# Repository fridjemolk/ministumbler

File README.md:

# ministumbler, a tiny ESP32 WiFi stumbling tool

This repo contains arduino code, helper python scripts, KiCad and Gerber Files, and hardware information about my ESP32 based WiFi stumbler, designed with low cost, minimal size, and easy of asssembly in mind. It is currently based around the Seeed XIAO/Adafruit QT Py ecosystem.

As of 02/2026, this project exists in 3 different hardware configurations, all of which are based on a GNSS Module, a MicroSD card slot, and a Xiao ESP32-S3:

#### v0.2: A custom PCB backplane supporting each of the modules, plus a [LiPo battery](https://thepihut.com/products/2000mah-3-7v-lipo-battery) charged by the Xiao ESP32-S3's built-in charge circuit, designed to fit into [this case from the Pi Hut](https://thepihut.com/products/small-plastic-project-enclosure-weatherproof-with-clear-top). The KiCad and Gerber files are [available here.](https://github.com/fridjemolk/ministumbler/tree/master/ministumbler_weatherproof_case) 

#### v0.1: A custom flex PCB backplane, supporting each of the modules, designed for stealthy use in the pocket of a bag or inside clothing. The KiCad and Gerber files are [available here.](https://github.com/fridjemolk/ministumbler/tree/master/ministumbler_kicad)

#### v0: A soldered-together stack of all three modules into a very compact rough cube shape. This was the initial prototype and is a little awkward to assemble as it requires deliberately not soldering certain pins for each module. 

All three hardware versions currently [use the same firmware](https://github.com/fridjemolk/ministumbler/blob/master/Ministumbler_WiGLE/Ministumbler_WiGLE.ino), with the same pin configurations, requireing the TX jumper pad to be **CUT** on the SD module and the A1 jumper pad **SOLDERED**. This firmware builds off the firmware created by [lozaning](https://github.com/lozaning) for their [Wifydra Project](https://github.com/lozaning/The_Wifydra), so credit to them for all their hard work in supporting the WiGLE CSV format and handling SD card file creation and management. 

[As of 02/2026, this is the main firmware used for this project](https://github.com/fridjemolk/ministumbler/blob/master/Ministumbler_WiGLE/Ministumbler_WiGLE.ino)

### Required Hardware

#### In the current design version the following three boards are used:

- [Seeed XIAO ESP32S3.](https://wiki.seeedstudio.com/xiao_esp32s3_getting_started/) The S3 variant of the ESP32 has the added benefit of Bluetooth support, and of having a U.FL connector for an external antenna, opening up options for optimising reception. Alternatively, the [Seeed XIAO ESP32C5](https://www.seeedstudio.com/Seeed-Studio-XIAO-ESP32C5-p-6609.html) can be used if 5GHz WiFi support is required, as both boards use the same pinout, however 5GHz is not yet supported by the firmware in this repo.
- [L76K GNSS Module for SeeedStudio XIAO.](https://wiki.seeedstudio.com/get_start_l76k_gnss/) A low-cost, TinyGPS++ compatible GPS module that has proven easy to use and quick to lock. Includes an active GPS antenna, also connected via a U.Fl connector
- [Adafruit microSD Card BFF.](https://learn.adafruit.com/adafruit-microsd-card-bff) A basic microSD card breakout board from adafruit that directly connects an insterted microSD to the SPI pins on the ESP32S3. Since the ESP32S3 has an on-board 3.3v regulator and runs at a 3.3v logic level there is no need for any regulator or level shifter to interface with a microSD card.

The v0 hardware design leads to an issue with the GPS RESET pin being the same as the MOSI (D10) pin of the ESP32, which is used to communicate with the microSD card. For the **v0 configuration ONLY** it is therefore required to ensure that this pin from the ESP32 connects only to the SD board, as the GPS RESET pin is not needed. In fact, the GPS module only requires it's RX, TX, 5V, GND, and 3v3 pins to actually be connected to the ESP32. The 5V pin can also be omitted to disabled the green GPS PPS LED if required.

Optionally, a 3.7V lithium battery can be used to power the device via the BAT +/- pins on the back of the Xiao board, which allow for both powering the Xiao board itself and any devices using it's 3.3v rail (note that no 5v power is available when running on battery), and also for charging the battery over the Xiao's USB-C port - [see this section of the Seeed wiki for more info](https://wiki.seeedstudio.com/xiao_esp32s3_getting_started/#battery-usage). This requires a battery connector being soldered to these pins. In the pictured v0.2 configuration, the pin headers included with the Xiao have been used to solder it to the PCB so as to use the plastic spacer on the headers to allow for the battery wires to reach the BAT +/- pins on the back of the Xiao board. In future this may be updated to use SMD soldering to connect these battery pins to a dedicated battery connector on the board. [This 2000mAh battery](https://thepihut.com/products/2000mah-3-7v-lipo-battery?variant=42143258050755) can power the device for several days in the v0.2 configuration. [This battery connector cable](https://thepihut.com/products/jst-ph-2-pin-cable-male-header-200mm?variant=12364083396670) was used to solder to the Xiao board, and power is applied or removed to the device by simple disconnecting the battery. 

## Software

### This repo, as it currently stands, contains three pieces of software:

- [A fully fledged WiGLE scanning script](https://github.com/fridjemolk/ministumbler/blob/master/Ministumbler_WiGLE/Ministumbler_WiGLE.ino), that scans all wifi channels and creats a WiGLE format CSV that can be uploaded to the WiGLE website.
- [A deprecated, more basic Arduino sketch](https://github.com/fridjemolk/ministumbler/blob/master/GPS_WiFi_XIAO_Serial_CSV/GPS_WiFi_XIAO_Serial_CSV.ino) that interfaces with the GPS module via the ESP32 fork of TinyGPSPlus and uses the Arduino WiFi libray to scan WiFi networks. The sketch will repeatedly generate a line of scanned CSV data with the current GPS location, date, time, and a list of WiFi SSIDs and either output it over USB Serial or save it to a MicroSD card. 
- [A simple python script](https://github.com/fridjemolk/ministumbler/blob/master/csv_write_test.py) that records the data received from the ESP32 over USB Serial and writes it to a CSV file. 

## KiCad Projects

To open these projects in KiCad, clone this repo or download one of the kicad directories and open the `.kicad_pro` file located inside each folder from KiCad's GUI.

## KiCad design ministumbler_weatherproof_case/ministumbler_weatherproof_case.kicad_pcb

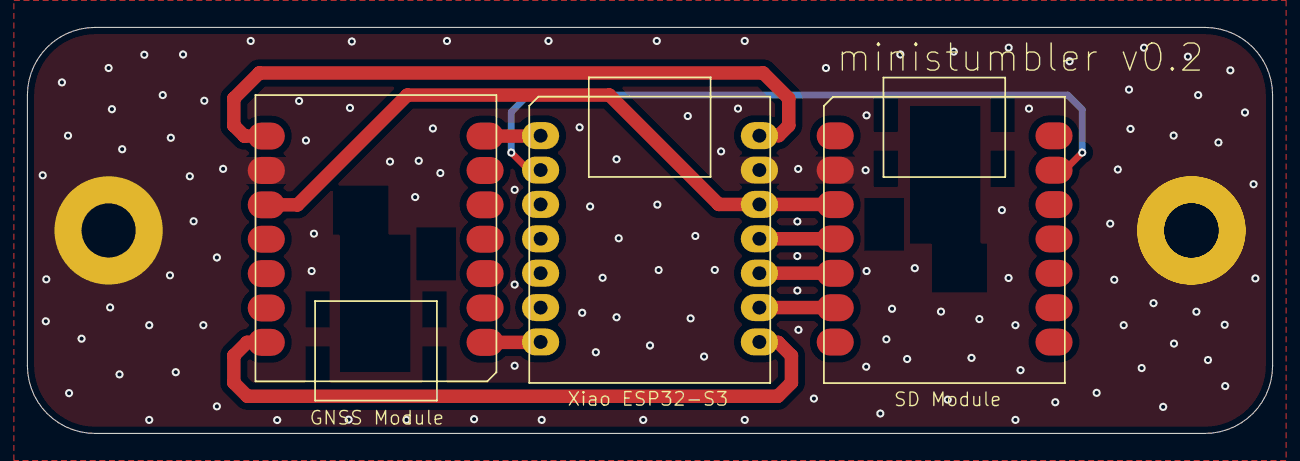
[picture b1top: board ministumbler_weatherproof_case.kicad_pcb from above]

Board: 2 copper layers, 92.0 x 30.0 mm, 3 parts (0 on the bottom side), 10 nets.

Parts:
ESP32: MOUDLE-SEEEDUINO-XIAO-ESP32S3; MOUDLE14P-SMD-2.54-21X17.8MM
GPS MODULE: MOUDLE-SEEEDUINO-XIAO-ESP32S3; MOUDLE14P-SMD-2.54-21X17.8MM
MICRO SD: MOUDLE-SEEEDUINO-XIAO-ESP32S3; MOUDLE14P-SMD-2.54-21X17.8MM

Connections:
+3V3: ESP32.12 (3V3), GPS MODULE.10 (PA5_A9_D9_MISO), MICRO SD.3 (PA10_A2_D2)
+5V: ESP32.14 (5V), GPS MODULE.8 (PB09_D7_RX)
GND: ESP32.13 (GND), GPS MODULE.9 (PA7_A8_D8_SCK), MICRO SD.2 (PA4_A1_D1)
GPS_WAKE: ESP32.1 (PA02_A0_D0), GPS MODULE.7 (PB08_A6_TX)
MISO: ESP32.10 (PA5_A9_D9_MISO), MICRO SD.5 (PA8_A4_D4_SDA)
MOSI: ESP32.11 (PA6_A10_D10_MOSI), MICRO SD.4 (PA11_A3_D3)
RX: ESP32.8 (PB09_D7_RX), GPS MODULE.14 (5V)
SCK: ESP32.9 (PA7_A8_D8_SCK), MICRO SD.6 (PA9_A5_D5_SCL)
SD_CS: ESP32.2 (PA4_A1_D1), MICRO SD.13 (GND)
TX: ESP32.7 (PB08_A6_TX), GPS MODULE.1 (PA02_A0_D0)

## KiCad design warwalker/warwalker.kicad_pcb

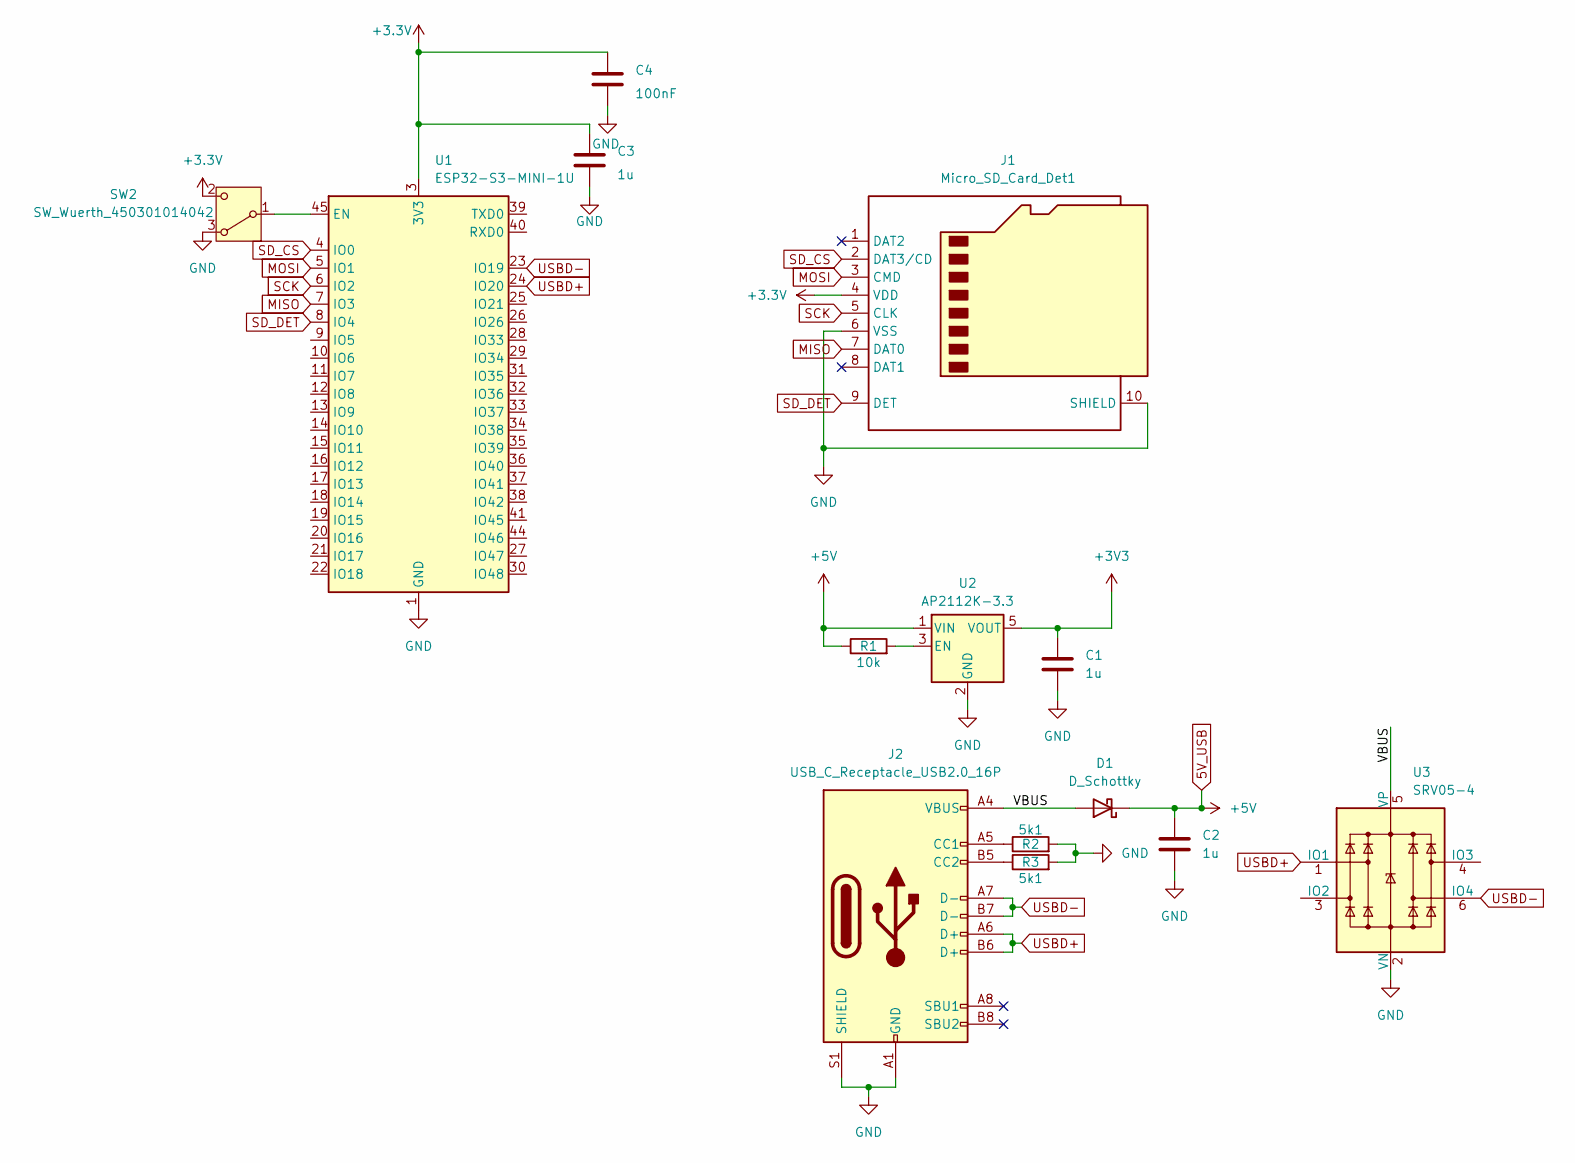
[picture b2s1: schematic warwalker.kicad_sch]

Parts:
C1, C2, C3: 1u; C_0201_0603Metric
C4: 100nF; C_0201_0603Metric
D1: D_Schottky; D_2114_3652Metric
J1: Micro_SD_Card_Det1; microSD_HC_Hirose_DM3D-SF
J2: USB_C_Receptacle_USB2.0_16P; USB_C_Receptacle_GCT_USB4105-xx-A_16P_TopMnt_Horizontal
R1: 10k; R_0201_0603Metric
R2, R3: 5k1; R_0201_0603Metric
SW2: SW_Wuerth_450301014042; SW_Slide-03_Wuerth-WS-SLTV_10x2.5x6.4_P2.54mm
U1: ESP32-S3-MINI-1U; ESP32-S2-MINI-1U
U2: AP2112K-3.3; SOT-23-5
U3: SRV05-4; SOT-23-6

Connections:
5V_USB: C2.1, D1.1 (K), R1.1, U2.1 (VIN)
+3.3V: C3.1, C4.1, J1.4 (VDD), SW2.2 (C), U1.3 (3V3)
+3V3: C1.1, U2.5 (VOUT)
/VBUS: D1.2 (A), J2.A4 (VBUS), J2.A9 (VBUS), J2.B4 (VBUS), J2.B9 (VBUS), U3.5 (VP)
GND: C1.2, C2.2, C3.2, C4.2, J1.6 (VSS), J1.10 (SHIELD), J2.A1 (GND), J2.A12 (GND), J2.B1 (GND), J2.B12 (GND), J2.S1 (SHIELD), R2.2, R3.2, SW2.3 (A), U1.1 (GND), U1.2 (GND), U1.42 (GND), U1.43 (GND), U1.46 (GND), U1.47 (GND), U1.48 (GND), U1.49 (GND), U1.50 (GND), U1.51 (GND), U1.52 (GND), U1.53 (GND), U1.54 (GND), U1.55 (GND), U1.56 (GND), U1.57 (GND), U1.58 (GND), U1.59 (GND), U1.60 (GND), U1.61 (GND), U1.62 (GND), U1.63 (GND), U1.64 (GND), U1.65 (GND), U2.2 (GND), U3.2 (VN)
MISO: J1.7 (DAT0), U1.7 (IO3)
MOSI: J1.3 (CMD), U1.5 (IO1)
unnamed: J2.A5 (CC1), R2.1
unnamed: J2.B5 (CC2), R3.1
unnamed: SW2.1 (B), U1.45 (EN)
unnamed: R1.2, U2.3 (EN)
SCK: J1.5 (CLK), U1.6 (IO2)
SD_CS: J1.2 (DAT3/CD), U1.4 (IO0)
SD_DET: J1.9 (DET), U1.8 (IO4)
USBD+: J2.A6 (D+), J2.B6 (D+), U1.24 (IO20), U3.1 (IO1)
USBD-: J2.A7 (D-), J2.B7 (D-), U1.23 (IO19), U3.6 (IO4)

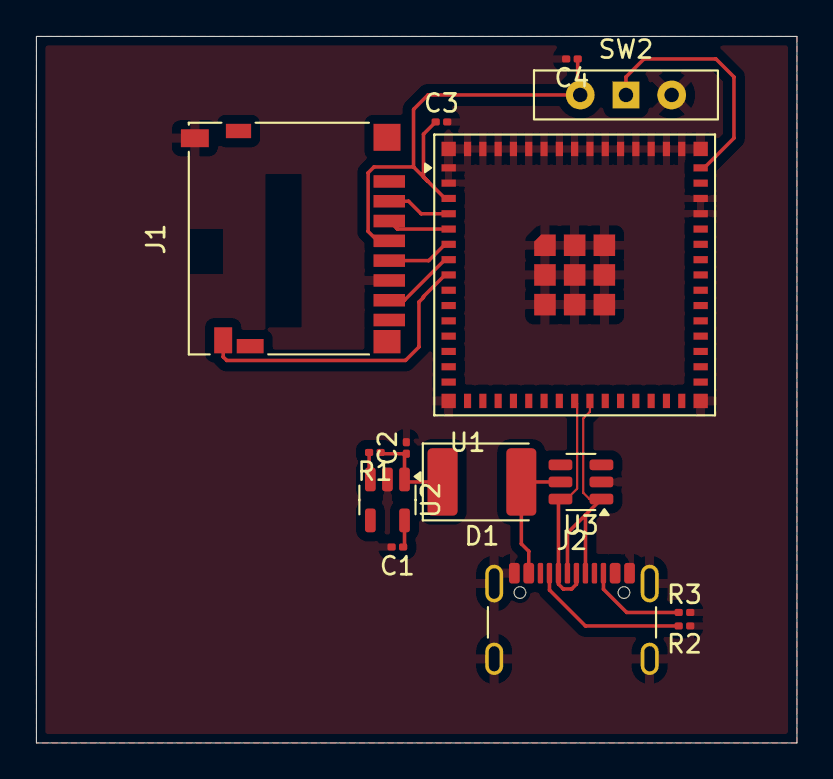
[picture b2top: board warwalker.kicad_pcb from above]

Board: 2 copper layers, 42.2 x 39.2 mm, 14 parts (0 on the bottom side), 16 nets.

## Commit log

2024-10-26 Added python serial parser
2024-10-26 Added arduino CSV serial sketch
2024-10-28 Added hardware and software details to README.md
    Added details of the first hardware and software versions of this project.
    TODO: Add an explanation of how to assemble the project
2024-10-28 Fixed README.md markdown
2024-11-02 Added intial flex pcb design
2024-11-02 Added KiCad info to README.md
2024-11-02 Added KiCad project
2024-11-02 Updated README.md with KiCad info
2024-11-02 Spelling
2024-12-09 Added additional code attribution
2025-02-06 Added MicroSD Support
2026-01-04 added kicad and gerber files
    added kicad and gerber files for the deaddrop weatherproof ministumbler variant
2026-02-06 Added WiGLE Arduino Sketch
2026-02-07 Updated CSV header
2026-02-09 Add TinyGPS++ Documentation Link
2026-02-10 Added L76K info link to Ministumbler_WiGLE.ino
2026-02-10 Added L76K command to use GLONASS at startup
2026-03-26 Switch WiFi scan to passive mode, updated CSV header
